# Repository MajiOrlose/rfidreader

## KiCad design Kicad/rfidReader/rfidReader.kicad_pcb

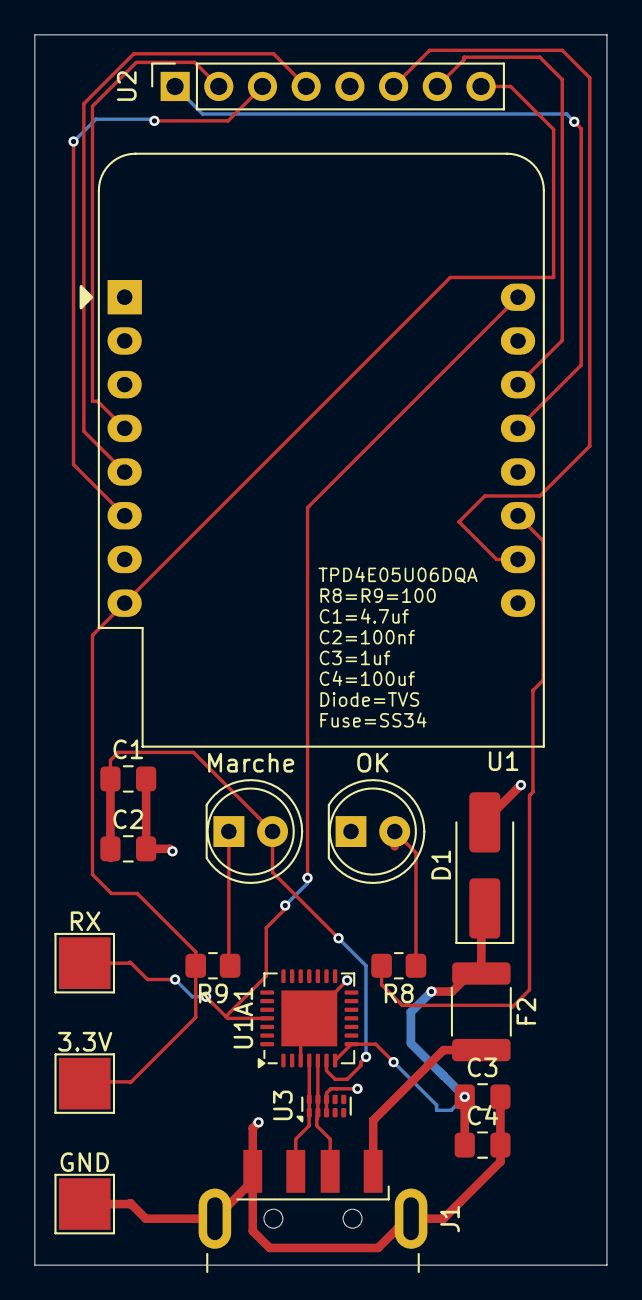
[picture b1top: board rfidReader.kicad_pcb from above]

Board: 2 copper layers, 33.2 x 71.5 mm, 18 parts (0 on the bottom side), 16 nets.

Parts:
3.3V: TestPoint; TestPoint_Pad_3.0x3.0mm
C1: 4.7uf; C_0805_2012Metric_Pad1.18x1.45mm_HandSolder
C2: 100nf; C_0805_2012Metric_Pad1.18x1.45mm_HandSolder
C3: 1uf; C_0805_2012Metric_Pad1.18x1.45mm_HandSolder
C4: 100uF; C_0805_2012Metric_Pad1.18x1.45mm_HandSolder
D1: DIODE_SHOTTKY*; D_SMA_Handsoldering
F2: Fuse; Fuse_1812_4532Metric_Pad1.30x3.40mm_HandSolder
GND: TestPoint; TestPoint_Pad_3.0x3.0mm
J1: USB_A; USB_A_CNCTech_1001-011-01101_Horizontal
Marche: LED; LED_D5.0mm
OK: LED; LED_D5.0mm
R8, R9: R; R_0805_2012Metric_Pad1.20x1.40mm_HandSolder
RX: TestPoint; TestPoint_Pad_3.0x3.0mm
U1: WEMOS_D1_mini; WEMOS_D1_mini_light
U1A1: VQFN-28-1EP_5x5mm_P0.5mm_EP3.25x3.25mm
U2: PinSocket_1x08_P2.54mm_Vertical
U3: TPD4E05U06DQA; USON-10_2.5x1.0mm_P0.5mm

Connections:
+5V: F2.2, J1.1 (VBUS)
/D4: R8.2, U1.11 (D4)
/D+: J1.3 (D+), U1A1.4 (D+), U3.1 (D1+), U3.10 (NC)
/D-: J1.2 (D-), U1A1.5 (D-), U3.2 (D1-), U3.9 (NC)
/RX: RX.1, U1.16 (TX), U1A1.25 (RXD)
GND: C1.2, C2.2, C3.2, C4.2, D1.2 (A), GND.1, J1.4 (GND), J1.5 (Shield), OK.1 (K), U1.10 (GND), U1A1.3 (GND), U1A1.29 (GND), U2.6 (GND), U3.3 (GND), U3.8 (GND)
unnamed: C1.1, C2.1, Marche.2 (A), U1A1.6 (VDD)
unnamed: Marche.1 (K), R9.1
unnamed: U1.5 (MISO/D6), U2.4 (MISO)
unnamed: U1.6 (MOSI/D7), U2.3 (MOSI)
unnamed: U1.4 (SCK/D5), U2.2 (SCK)
unnamed: U1.14 (SCL/D1), U2.7 (RST)
unnamed: U1.13 (SDA/D2), U2.1 (SDA)
unnamed: OK.2 (A), R8.1
VBUS: C3.1, C4.1, D1.1 (K), F2.1, U1A1.7 (REGIN), U1A1.8 (VBUS)
VDD: 3.3V.1, R9.2, U1.8 (3V3), U2.8 (3.3V)

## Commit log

2025-12-08 first
2025-12-11 Kicad
